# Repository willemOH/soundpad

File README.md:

Soundpad: tactile sampler instrument and sound sketchpad

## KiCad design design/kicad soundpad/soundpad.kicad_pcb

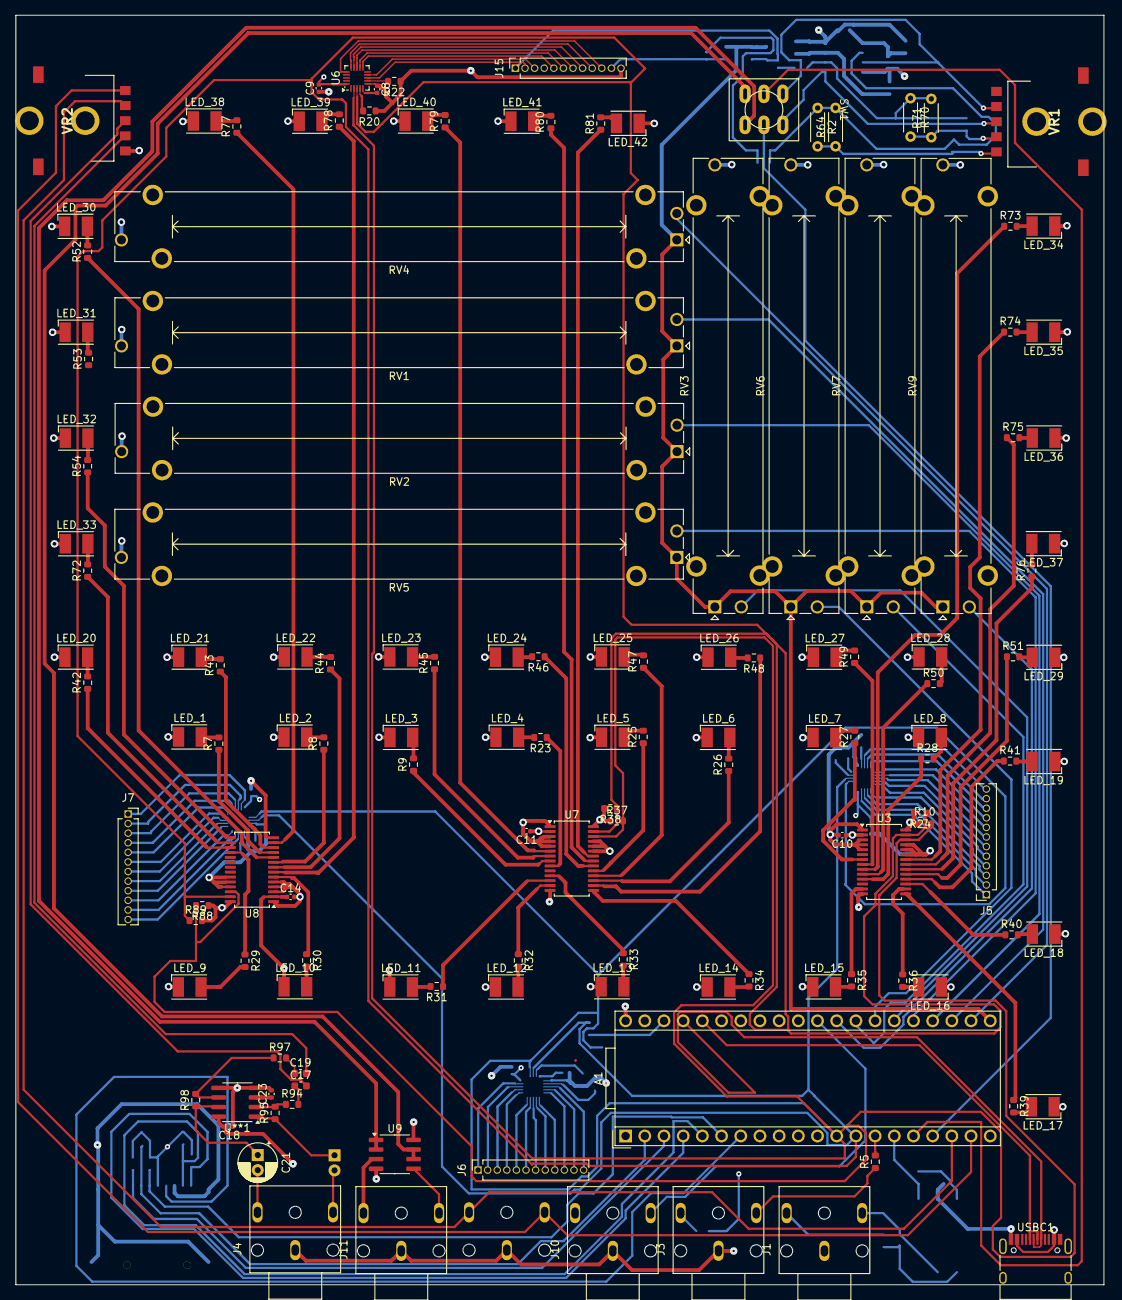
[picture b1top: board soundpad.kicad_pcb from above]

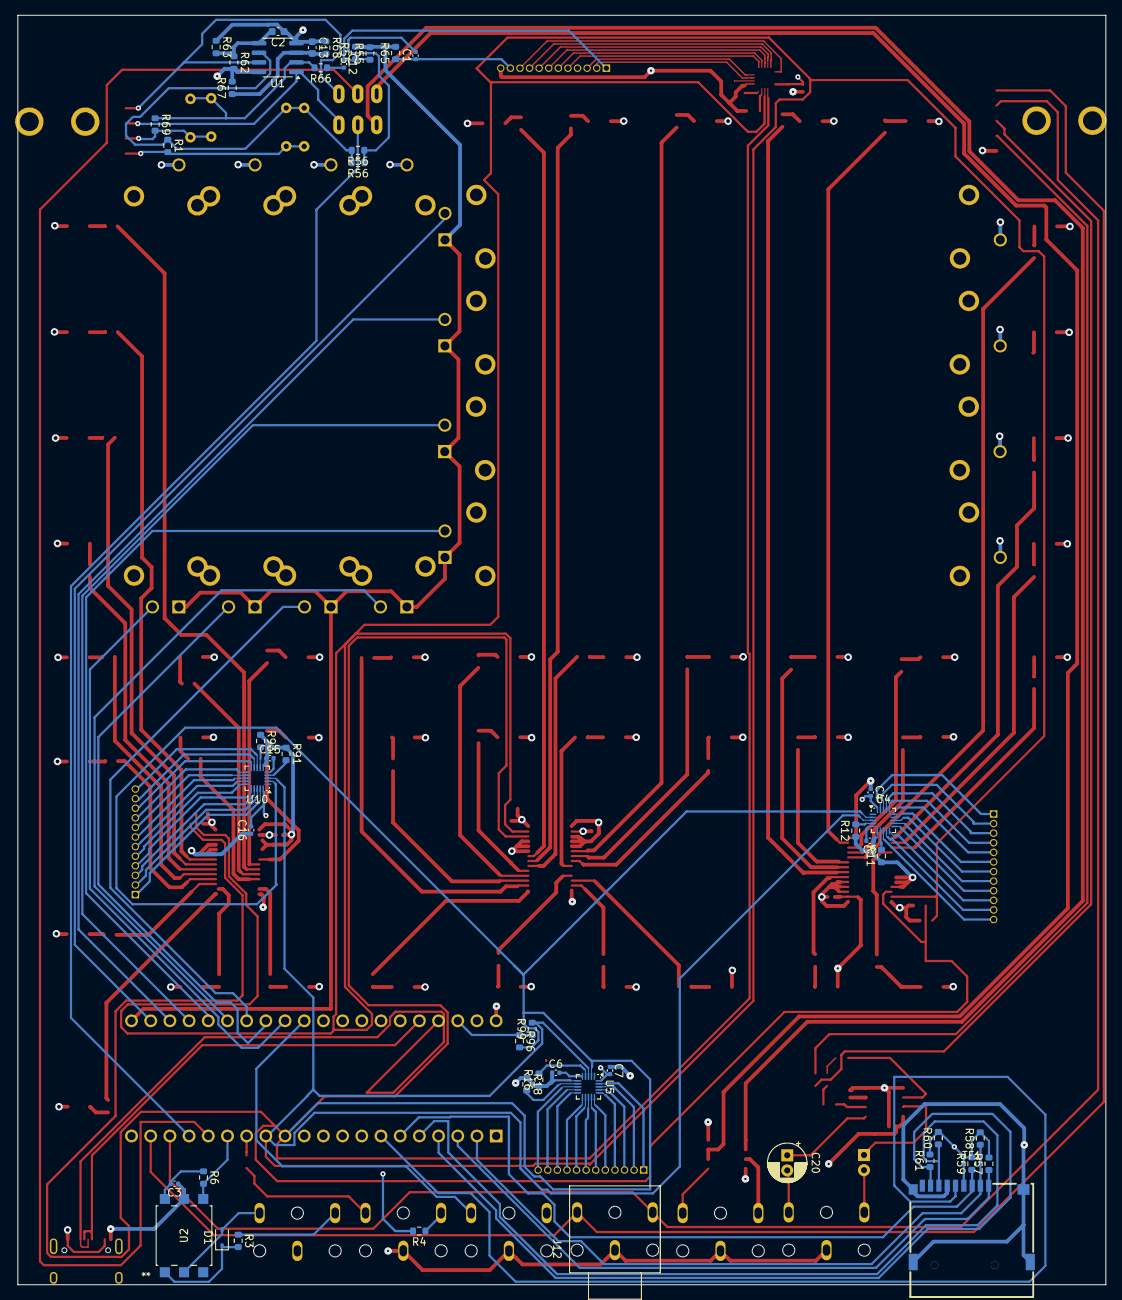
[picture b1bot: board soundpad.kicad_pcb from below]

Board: 4 copper layers, 144.0 x 168.0 mm, 187 parts (48 on the bottom side), 201 nets.

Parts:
A1: Electrosmith_Daisy_Seed_Rev4; Electrosmith_Daisy_Seed
C1, C3, C4, C5, C6, C7, C8, C9, C10, C11, C12, C14, C15, C16, C18, C23: 0.1uF; C_0402_1005Metric
C2, C13: 10uF; C_0603_1608Metric
C17, C19: .47uF; C_0603_1608Metric
C20, C21: 220UF PANASONIC D8; CP_Radial_D5.0mm_P2.00mm
D1: 1N4148WS; D_SOD-323
J1: Midi_In; CUI_SJ1-3553NG
J3: Midi_Out; CUI_SJ1-3553NG
J4: Headphone_Out; CUI_SJ1-3553NG
J5, J6, J7, J15: Conn_01x12_Socket; PinSocket_1x12_P1.27mm_Vertical
J10: Clock_Out; CUI_SJ1-3553NG
J11: Line_In; CUI_SJ1-3553NG
J12: Line_Out; CUI_SJ1-3553NG
LED_1, LED_2, LED_3, LED_4, LED_5, LED_6, LED_7, LED_8, LED_9, LED_10, LED_11, LED_12, LED_13, LED_14, LED_15, LED_16, LED_17, LED_18, LED_19, LED_20, LED_21, LED_22, LED_23, LED_24, LED_25, LED_26, LED_27, LED_28, LED_29, LED_30, LED_31, LED_32, LED_33, LED_34, LED_35, LED_36, LED_37, LED_38, LED_39, LED_40, LED_41, LED_42: White; LED_PLCC-2_3.4x3.0mm_AK
R1, R69: 10K; R_0603_1608Metric
R2, R64, R70, R71: DI*; R_Axial_DIN0204_L3.6mm_D1.6mm_P5.08mm_Horizontal
R3: 220R; R_0603_1608Metric
R4: 33R; R_0603_1608Metric
R5: 10R; R_0603_1608Metric
R6: 270R; R_0603_1608Metric
R7, R8, R9, R23, R25, R26, R27, R28, R29, R30, R31, R32, R33, R34, R35, R36, R39, R40, R41, R42, R43, R44, R45, R46, R47, R48, R49, R50, R51, R52, R53, R54, R72, R73, R74, R75, R76, R77, R78, R79, R80, R81: 140R; R_0603_1608Metric
R10, R24, R37, R38, R88, R89: 4.7K; R_0603_1608Metric
R11, R18, R22, R93: 75k; R_0603_1608Metric
R12, R16, R20, R91: 100k; R_0603_1608Metric
R55, R55#2, R65: 2.2K; R_0603_1608Metric
R56, R56#2, R66: 50R; R_0603_1608Metric
R57, R58, R59, R60, R61: 47k; R_0603_1608Metric
R62, R63, R67, R68: 100K; R_0603_1608Metric
R94, R97: 22K; R_0603_1608Metric
R95, R98: 33K; R_0603_1608Metric
R96, R99: 10k; R_0603_1608Metric
RV1: slider2; Potentiometer_Bourns_PTA6043_Single_Slide
RV2: slider3; Potentiometer_Bourns_PTA6043_Single_Slide
RV3: sliderA; Potentiometer_Bourns_PTA4543_Single_Slide
RV4: slider1; Potentiometer_Bourns_PTA6043_Single_Slide
RV5: slider4; Potentiometer_Bourns_PTA6043_Single_Slide
RV6: sliderB; Potentiometer_Bourns_PTA4543_Single_Slide
RV7: sliderC; Potentiometer_Bourns_PTA4543_Single_Slide
RV9: sliderD; Potentiometer_Bourns_PTA4543_Single_Slide
SW1: SW_DPDT_x2; Toggle Submini DPDT Prongs
TF1: TF-CARD H1.8; TF-SMD_TF-CARD-H1.8
U1, U9: MCP6002-xSN; SOIC-8_3.9x4.9mm_P1.27mm
U2: H11L1S(TA); H11L1STA_EVE
U3, U7, U8: PCA9685PW; TSSOP-28_4.4x9.7mm_P0.65mm
U4, U5, U6, U10: MPR121QR2; UQFN-20_3x3mm_P0.4mm
U**1: LM4881MX SOIC-8; SOIC-8_3.9x4.9mm_P1.27mm
USBC1: TYPE-C-31-M-12; USB_C_Receptacle_HRO_TYPE-C-31-M-12
VR1, VR2: RK10J12R0A0B

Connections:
3V3_A: A1.21 (3V3_A), C18.2, R55.2, R55#2.2, R65.2, RV1.1, RV2.1, RV3.1, RV4.1, RV5.1, RV6.1, RV7.1, RV9.1, U**1.8 (VCC)
3V3_D: A1.38 (3V3_D), C4.2, C7.2, C9.2, C16.2, R4.2, R57.2, R58.2, R59.2, R60.2, R61.2, R96.1, R99.1, TF1.4 (VDD), U4.20 (VDD), U5.20 (VDD), U6.20 (VDD), U10.20 (VDD)
5V: A1.39 (VIN), C10.1, C11.1, C14.1, LED_1.2 (A), LED_2.2 (A), LED_3.2 (A), LED_4.2 (A), LED_5.2 (A), LED_6.2 (A), LED_7.2 (A), LED_8.2 (A), LED_9.2 (A), LED_10.2 (A), LED_11.2 (A), LED_12.2 (A), LED_13.2 (A), LED_14.2 (A), LED_15.2 (A), LED_16.2 (A), LED_17.2 (A), LED_18.2 (A), LED_19.2 (A), LED_20.2 (A), LED_21.2 (A), LED_22.2 (A), LED_23.2 (A), LED_24.2 (A), LED_25.2 (A), LED_26.2 (A), LED_27.2 (A), LED_28.2 (A), LED_29.2 (A), LED_30.2 (A), LED_31.2 (A), LED_32.2 (A), LED_33.2 (A), LED_34.2 (A), LED_35.2 (A), LED_36.2 (A), LED_37.2 (A), LED_38.2 (A), LED_39.2 (A), LED_40.2 (A), LED_41.2 (A), LED_42.2 (A), R10.2, R24.2, R37.2, R38.2, R62.2, R67.2, R88.2, R89.2, U1.8 (V+), U3.2 (A1), U3.28 (VDD), U7.2 (A1), U7.28 (VDD), U8.2 (A1), U8.28 (VDD), U9.8 (V+), USBC1.A4 (VBUS), USBC1.A9 (VBUS), USBC1.B4 (VBUS), USBC1.B9 (VBUS)
+3.3V: C3.2, R6.1, U2.6
/Audio_IO/Headphone_Out_L: C20.2, J4.T
/Audio_IO/Headphone_Out_R: C21.2, J4.R
/Audio_IO/Headphone_Wiper_L: C17.2, VR2.2 (2_1)
/Audio_IO/Headphone_Wiper_R: C19.2, VR2.4 (2_2)
/IO_SDcard/Line_In_L: SW1.3 (C), U9.6 (-), U9.7
/IO_SDcard/Line_In_R: SW1.6 (C), U9.1, U9.2 (-)
/IO_SDcard/mic_out_L: SW1.1 (A), U1.7, VR1.4 (2_2)
/IO_SDcard/mic_out_R: SW1.4 (A), U1.1, VR1.2 (2_1)
/LEDs/LED_1: R7.1, U8.11 (LED5)
/LEDs/LED_2: R8.1, U8.9 (LED3)
/LEDs/LED_3: R9.1, U7.8 (LED2)
/LEDs/LED_4: R23.1, U7.9 (LED3)
/LEDs/LED_5: R25.1, U7.19 (LED12)
/LEDs/LED_6: R26.1, U7.17 (LED10)
/LEDs/LED_7: R27.1, U3.7 (LED1)
/LEDs/LED_8: R28.1, U3.11 (LED5)
/LEDs/LED_9: R29.1, U8.18 (LED11)
/LEDs/LED_10: R30.1, U8.6 (LED0)
/LEDs/LED_11: R31.1, U7.12 (LED6)
/LEDs/LED_12: R32.1, U7.13 (LED7)
/LEDs/LED_13: R33.1, U7.11 (LED5)
/LEDs/LED_14: R34.1, U7.15 (LED8)
/LEDs/LED_15: R35.1, U3.13 (LED7)
/LEDs/LED_16: R36.1, U3.16 (LED9)
/LEDs/LED_17: R39.1, U3.15 (LED8)
/LEDs/LED_18: R40.1, U3.17 (LED10)
/LEDs/LED_19: R41.1, U3.18 (LED11)
/LEDs/LED_20: R42.1, U8.17 (LED10)
/LEDs/LED_21: R43.1, U8.12 (LED6)
/LEDs/LED_22: R44.1, U8.8 (LED2)
/LEDs/LED_23: R45.1, U7.7 (LED1)
/LEDs/LED_24: R46.1, U7.20 (LED13)
/LEDs/LED_25: R47.1, U7.18 (LED11)
/LEDs/LED_26: R48.1, U7.16 (LED9)
/LEDs/LED_27: R49.1, U3.8 (LED2)
/LEDs/LED_28: R50.1, U3.10 (LED4)
/LEDs/LED_29: R51.1, U3.19 (LED12)
/LEDs/LED_30: R52.1, U8.10 (LED4)
/LEDs/LED_32: R54.1, U8.15 (LED8)
/LEDs/LED_33: R72.1, U8.16 (LED9)
/LEDs/LED_34: R73.1, U3.9 (LED3)
/LEDs/LED_35: R74.1, U3.22 (LED15)
/LEDs/LED_36: R75.1, U3.21 (LED14)
/LEDs/LED_37: R76.1, U3.20 (LED13)
/LEDs/LED_38: R77.1, U8.13 (LED7)
/LEDs/LED_39: R78.1, U8.7 (LED1)
/LEDs/LED_40: R79.1, U7.6 (LED0)
/LEDs/LED_41: R80.1, U7.21 (LED14)
/LEDs/LED_42: R81.1, U7.22 (LED15)
AMP: J7.5, U4.15 (LED3/ELE7)
Audio_in_1: A1.16 (AUDIO_IN_1), SW1.2 (B)
Audio_in_2: A1.17 (AUDIO_IN_2), SW1.5 (B)
Audio_out_1: A1.18 (AUDIO_OUT_1), J12.T, VR2.3 (3_1)
Audio_out_2: A1.19 (AUDIO_OUT_2), J12.R, VR2.5 (3_2)
COMP: J5.7, U10.13 (LED1/ELE5)
Clock_out: A1.30 (DAC_OUT1), J10.T
D+: A1.37 (USB_D_+), USBC1.A6 (DP1), USBC1.B6 (DP2)
D-: A1.36 (USB_D_-), USBC1.A7 (DN1), USBC1.B7 (DN2)
EFFCT: J5.6, U10.14 (LED2/ELE6)
Extra1: J6.8, U5.12 (LED0/ELE4)
Extra2: J6.9, U5.11 (ELE3)
Extra3: J6.10, U5.10 (ELE2)
FILT: J7.6, U4.14 (LED2/ELE6)
GND: A1.20 (AGND), A1.40 (DGND), C2.1, C3.1, C4.1, C5.1, C6.1, C7.1, C8.1, C9.1, C10.2, C11.2, C13.1, C14.2, C15.1, C16.1, C18.1, C23.2, J3.S, J4.S, J10.S, J11.S, J12.S, J15.12, R11.1, R12.1, R16.1, R18.1, R20.1, R22.1, R63.1, R68.1, R91.1, R93.1, RV1.3, RV2.3, RV3.3, RV4.3, RV5.3, RV6.3, RV7.3, RV9.3, TF1.6 (VSS), TF1.10 (GND), TF1.11 (GND), TF1.12 (GND), TF1.13 (GND), U1.4 (V-), U2.5, U3.1 (A0), U3.3 (A2), U3.4 (A3), U3.5 (A4), U3.14 (VSS), U3.23 (~OE), U3.24 (A5), U3.25 (EXTCLK), U4.6 (VSS), U5.6 (VSS), U6.6 (VSS), U7.1 (A0), U7.3 (A2), U7.4 (A3), U7.5 (A4), U7.14 (VSS), U7.23 (~OE), U7.24 (A5), U7.25 (EXTCLK), U8.1 (A0), U8.3 (A2), U8.4 (A3), U8.5 (A4), U8.14 (VSS), U8.23 (~OE), U8.24 (A5), U8.25 (EXTCLK), U9.4 (V-), U10.6 (VSS), U**1.4 (GND), U**1.5 (SDOWN), USBC1.A1 (GND), USBC1.B12 (GND), VR2.1 (1/1)
MIDI_RX: A1.15 (USART1_RX), R6.2, U2.4
MIDI_TX: A1.14 (USART1_TX), R5.2
MOD: J7.7, U4.13 (LED1/ELE5)
MicL: C1.1, J15.11, R65.1
MicR: C12.1, J15.1, R55.1, R55#2.1
unnamed: A1.22 (ADC_0), RV4.2
unnamed: A1.23 (ADC_1), RV1.2
unnamed: A1.24 (ADC_2), RV2.2
unnamed: A1.25 (ADC_3), RV5.2
unnamed: A1.26 (ADC_4), RV3.2
unnamed: A1.27 (ADC_5), RV6.2
unnamed: A1.28 (ADC_6), RV7.2
unnamed: A1.29 (DAC_OUT2), RV9.2
unnamed: C1.2, R56.1, R56#2.1
unnamed: C12.2, R66.1
unnamed: C17.1, R94.2
unnamed: C19.1, R97.2
unnamed: D1.2 (A), J1.T, U2.2
unnamed: D1.1 (K), R3.2, U2.1
unnamed: J1.R, R3.1
unnamed: J3.R, R4.1
unnamed: J3.T, R5.1
unnamed: LED_1.1 (K), R7.2
unnamed: LED_2.1 (K), R8.2
unnamed: LED_3.1 (K), R9.2
unnamed: LED_4.1 (K), R23.2
unnamed: LED_5.1 (K), R25.2
unnamed: LED_6.1 (K), R26.2
unnamed: LED_7.1 (K), R27.2
unnamed: LED_8.1 (K), R28.2
unnamed: LED_9.1 (K), R29.2
unnamed: LED_10.1 (K), R30.2
unnamed: LED_11.1 (K), R31.2
unnamed: LED_12.1 (K), R32.2
unnamed: LED_13.1 (K), R33.2
unnamed: LED_14.1 (K), R34.2
unnamed: LED_15.1 (K), R35.2
unnamed: LED_16.1 (K), R36.2
unnamed: LED_17.1 (K), R39.2
unnamed: LED_18.1 (K), R40.2
unnamed: LED_19.1 (K), R41.2
unnamed: LED_20.1 (K), R42.2
unnamed: LED_21.1 (K), R43.2
unnamed: LED_22.1 (K), R44.2
unnamed: LED_23.1 (K), R45.2
unnamed: LED_24.1 (K), R46.2
unnamed: LED_25.1 (K), R47.2
unnamed: LED_26.1 (K), R48.2
unnamed: LED_27.1 (K), R49.2
unnamed: LED_28.1 (K), R50.2
unnamed: LED_29.1 (K), R51.2
unnamed: LED_30.1 (K), R52.2
unnamed: LED_31.1 (K), R53.2
unnamed: LED_32.1 (K), R54.2
unnamed: LED_33.1 (K), R72.2
unnamed: LED_34.1 (K), R73.2
unnamed: LED_35.1 (K), R74.2
unnamed: LED_36.1 (K), R75.2
unnamed: LED_37.1 (K), R76.2
unnamed: LED_38.1 (K), R77.2
unnamed: LED_39.1 (K), R78.2
unnamed: LED_40.1 (K), R79.2
unnamed: LED_41.1 (K), R80.2
unnamed: LED_42.1 (K), R81.2
unnamed: C13.2, R67.1, R68.2, U1.3 (+)
unnamed: R66.2, R69.1, R70.1, R71.2, U1.2 (-)
unnamed: C2.2, R62.1, R63.2, U1.5 (+)
unnamed: R1.1, R2.1, R56.2, R56#2.2, R64.2, U1.6 (-)
unnamed: R12.2, U4.4 (ADDR)
unnamed: R11.2, U4.7 (REXT)
unnamed: C5.2, U4.5 (VREG)
unnamed: R16.2, U5.4 (ADDR)
unnamed: R18.2, U5.7 (REXT)
unnamed: C6.2, U5.5 (VREG)
unnamed: R20.2, U6.4 (ADDR)
unnamed: R22.2, U6.7 (REXT)
unnamed: C8.2, U6.5 (VREG)
unnamed: J11.R, U9.3 (+)
unnamed: J11.T, U9.5 (+)
unnamed: R91.2, U10.4 (ADDR)
unnamed: R93.2, U10.7 (REXT)
unnamed: C15.2, U10.5 (VREG)
unnamed: C23.1, U**1.3 (BPASS)
unnamed: R94.1, R95.2, U**1.2 (IN1)
unnamed: R97.1, R98.2, U**1.6 (IN2)
unnamed: C20.1, R95.1, U**1.1 (OUT1)
unnamed: C21.1, R98.1, U**1.7 (OUT2)
unnamed: R69.2, R70.2, R71.1, VR1.3 (3_1)
unnamed: R1.2, R2.2, R64.1, VR1.5 (3_2)
POUCH: J5.9, U10.11 (ELE3)
Pad1: J7.11, U4.9 (ELE1)
Pad2: J7.10, U4.10 (ELE2)
Pad3: J7.9, U4.11 (ELE3)
Pad4: J7.8, U4.12 (LED0/ELE4)
Pad5: J5.5, U10.15 (LED3/ELE7)
Pad6: J5.4, U10.16 (LED4/ELE8)
Pad7: J5.3, U10.17 (LED5/ELE9)
Pad8: J5.2, U10.18 (LED6/ELE10)
Pad9: J7.12, U4.8 (ELE0)
Pad10: J6.1, U5.19 (LED7/ELE11)
Pad11: J6.2, U5.18 (LED6/ELE10)
Pad12: J6.3, U5.17 (LED5/ELE9)
Pad13: J6.4, U5.16 (LED4/ELE8)
Pad14: J6.5, U5.15 (LED3/ELE7)
Pad15: J6.6, U5.14 (LED2/ELE6)
Pad16: J6.7, U5.13 (LED1/ELE5)
PadAfter: J15.8, U6.14 (LED2/ELE6)
PadEmpty: J5.10, U10.10 (ELE2)
PadFlow: J15.5, U6.11 (ELE3)
PadGroups: J5.1, U10.19 (LED7/ELE11)
PadL1: J15.10, U6.16 (LED4/ELE8)
PadL2: J15.9, U6.15 (LED3/ELE7)
PadL3: J7.1, U4.19 (LED7/ELE11)
PadL4: J7.2, U4.18 (LED6/ELE10)
PadMod: J15.6, U6.12 (LED0/ELE4)
PadNotes: J6.12, U5.8 (ELE0)
PadPattern: J6.11, U5.9 (ELE1)
PadPocket: J7.3, U4.17 (LED5/ELE9)
PadR1: J15.2, U6.8 (ELE0)
PadR2: J15.3, U6.9 (ELE1)
PadR3: J5.12, U10.8 (ELE0)
PadR4: J5.11, U10.9 (ELE1)
PadVelo: J15.7, U6.13 (LED1/ELE5)
SCL: A1.12 (I2C1_SCL), R10.1, R37.1, R88.1, R96.2, U3.26 (SCL), U4.2 (SCL), U5.2 (SCL), U6.2 (SCL), U7.26 (SCL), U8.26 (SCL), U10.2 (SCL)
SCRATCH: J5.8, U10.12 (LED0/ELE4)
SDA: A1.13 (I2C1_SDA), R24.1, R38.1, R89.1, R99.2, U3.27 (SDA), U4.3 (SDA), U5.3 (SDA), U6.3 (SDA), U7.27 (SDA), U8.27 (SDA), U10.3 (SDA)
SD_CK: A1.7 (SD_CLK), TF1.5 (CLK)
SD_CMD: A1.6 (SD_CMD), R59.1, TF1.3 (CMD)
SD_D0: A1.5 (SD_DATA_0), R60.1, TF1.7 (DAT0)
SD_D1: A1.4 (SD_DATA_1), R61.1, TF1.8 (DAT1)
SD_D2: A1.3 (SD_DATA_2), R57.1, TF1.1 (DAT2)
SD_D3: A1.2 (SD_DATA_3), R58.1, TF1.2 (CD/DAT3)
SOUND: J7.4, U4.16 (LED4/ELE8)

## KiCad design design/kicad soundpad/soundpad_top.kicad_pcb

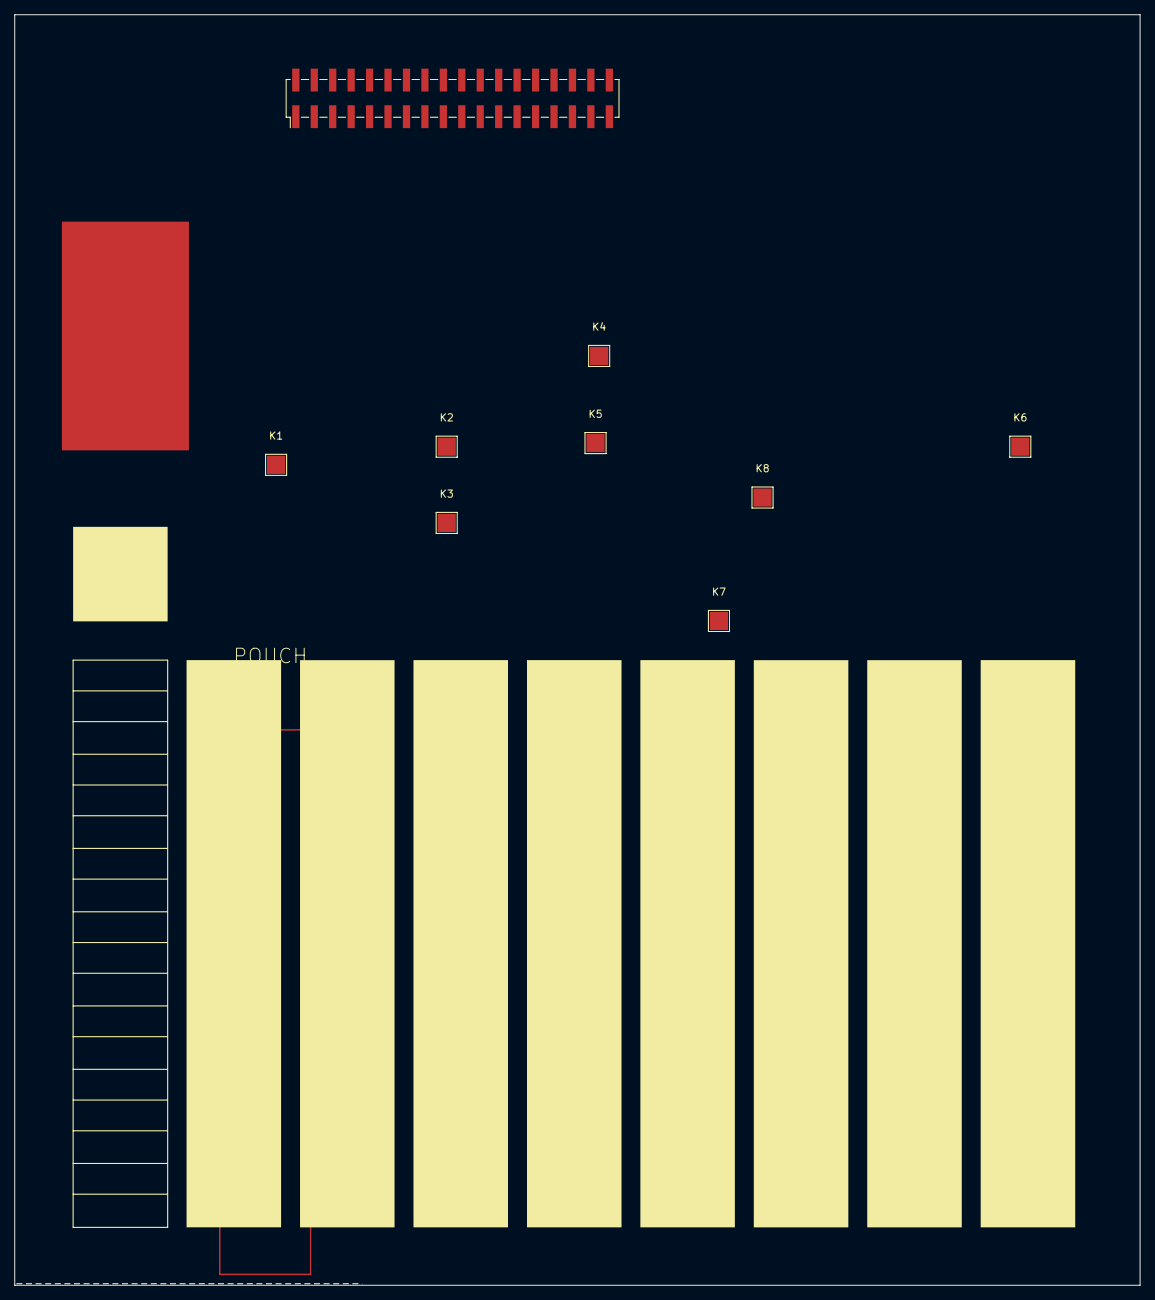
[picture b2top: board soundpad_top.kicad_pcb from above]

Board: 2 copper layers, 155.0 x 175.0 mm, 9 parts (0 on the bottom side), 8 nets, no tracks yet.

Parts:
J2: Conn_02x18_Counter_Clockwise; PinHeader_2x18_P2.54mm_Vertical_SMD
K1, K2, K3, K4, K5, K6, K7, K8: Conn_01x01; TestPoint_Pad_2.5x2.5mm

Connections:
unnamed: J2.1, K1.1
unnamed: J2.3, K2.1
unnamed: J2.5, K3.1
unnamed: J2.7, K4.1
unnamed: J2.9, K5.1
unnamed: J2.11, K6.1
unnamed: J2.13, K7.1
unnamed: J2.15, K8.1

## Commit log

2024-08-17 first
2024-08-17 tests button
2024-08-17 stops tracking build directory
2024-08-17 saving changes before continuing rebase
2024-08-17 updates readme to project mission
2024-08-17 adds .gitignore, untracks build dir, updates readme
2024-08-17 changes project name
2024-08-18 adds sampling base, audio pass through while button pressed
2024-08-18 adds serial monitoring
2024-08-18 solves buffer recording, playback, looping is now a one button app fun remixer that adds input to looping buffer whenever button is held down
2024-08-19 serial monitoring off by default
2024-08-24 'normal' looping sampler
2024-08-24 adds to .gitignore
2024-08-24 fixes test tone playback on start
2024-08-24 refactors for basic stereo buffer class
2024-08-24 refactors bufferStereo.h for encapsulation
2024-08-24 cleans up main.cpp
2024-08-24 Introduces buffer chunks
    Allocates sample index ranges (chunks) from main buffers to be accessed from one of 16 objects which handles that chunk. Current setup performs the same as previous; no limits to keep recording withi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
2024-08-25 renames chunk-related info
2024-09-24 refactors sampling engine to new class
2024-09-25 cleans up comments, indentations, brackets
2024-09-25 refactors for hardware and ui encapsulation
    known bugs as of commit # 882fd294f44948a071e54f15eadf9aa652485573 (refactors sampling engine to new class):
    - loop start point is incorrect on first playback
    - sometimes does not playback loop, seemingly moreso if loop recorded is shorter than previous one
2024-09-25 Fixes bug, improves logic, cleans comments
    fixes shorter recording blank bug, evens bufferchunks divisions, removes bugtesting comments and old logic commented out
2024-09-26 Removes observer pattern, stops logging
2024-09-26 Separates finally sample engine from main
2024-09-27 Adds signal reference passing, global hardware object, optional float printing
2024-09-27 adds dev log file
2024-09-27 Encapsulates sample engine more, turns off logging, tidies comments
2024-09-27 v0.1: live remixer
    button1: record, button2: playback, button2+button1: playback loop on, live audio comes through when playback is not engaged
2024-09-28 Added interface.drawio
2024-09-28 Adds design directory, moves interface file
2024-09-30 Adds plate connections to pcb board
2024-09-30 v0.1: live remixer standalone
    turns off debugging so program can run without monitor connection
2024-10-04 Adds slider controls for sample start and end
2024-10-04 Updates kicad schematic for prototyping
    not a full schematic just all necessary parts to check off for a mouser order to set up a capactive touch prototype with midi in, out, and mic in
2024-10-04 renames variables, adds future hardware, makes functions private
2024-10-05 reduces function call rate
2024-10-07 adds start and end preview
    when sliders are moved a certain amount, a short preview of where the slider is in the continuum of the sample is played. This preview depends slightly on whether it is the start or end slider moved.
2024-10-07 resets start and end on record. Optimizes variable setting
2024-10-07 Increases slider resolution when loop is on
    bypasses threshold value for slider to change start and end
2024-10-08 adds speed change
    speed changes and triggers playback with play button + slider 1
2024-10-08 adds note play and note transpose
    play button + slider 2 increases pitch of sample by a scaled note increment. Current bug: speed changes are not what is played but the speed + note increment. so what you hear is not what you get
2024-10-10 Refactors sample settings to own file, design comments
2024-10-11 Refactors playback in sample class to own class
    Messy but functional refactor setting the stage for multiple simultaneous playback processes (polyphony). Sample class functions change playback class members when setting start or end (not ideal)
2024-10-18 Refactors buttons for capacitive touch
    A proud bit of work I must say. Ui class is streamlined by using button numbers directly instead of a struct. Binary operations and raw arrays replace library and vector functions for greater computa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
2024-10-19 Fixes button mash bug, adds 12-button objects
    When mashing buttons (intentionally try to break it), a button would not be removed and get stuck in the array. This fix checks for that and resets the array. Also adding back in an enum class that g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
2024-10-19 adds sliders 3 and 4
2024-10-22 adds continuous speed change, 10 buttons controls, less combos, design notes
    commands distributed over more buttons with commands behavior refined to give expected auditory results. See sp_ui.cpp for new command assignments.
2024-10-22 adds record to sd card test
    will record to sd card whatever is going out audio callback and then save the file on button 10 press. Works pretty flawlessly when logging is enabled. When not, no sound comes through input unless a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
2024-10-23 changes sd writing duration to record duration
    whatever is recorded to buffer which 'record' button is pressed is now also written (or overwritten) to a new file on the sd card. Additonal WriteProcess() function added because Process() is called 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
2024-10-25 refactors buffer to be interleaved
    For the purposes of easier transfer to wav files and back. Additionally, sample time increased due to writing 16-bit (current wav management limitation) instead of 24-bit audio and new calculations (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
2024-11-06 design updates
2024-11-06 fixes no startup if no sd card
2024-11-08 Refactors design for flat schematic, adds capactive touch, LCSC parts
    did not use bss138 level shifters and regulated 3.3v supply from adafruit schematic because daisy seed already has 3.3v regulated supply and 5V is not used internally on seed
2024-11-08 Completes all capacitive touch schematic work
    3x capacitive touch ics and routing to pins
2024-11-12 adds LEDs to design schematic
2024-12-11 completes kicad schematic, starts pcb layout
2025-01-18 routes PCB all except PWR
2025-01-18 gitignore kicad backups
2025-01-18 PCB all routed, Moves top components to top file
2025-01-18 gitignore kicad top backups
2025-01-24 shortens SD data lines
2025-01-27 adds debug log categorization
    new function to encapsulate hardware logging, now a globally accessible function. More logging/conversion to new logging of buttons pressed
2025-01-29 pcb rules fixes, reroute suggestions
2025-01-31 PCB moves analog signals to back plane
    so that ground plane inbetween them and digital signals. Also moves digital signals away from back plane and instead weaves them between the two top planes.
2025-03-26 last commit before refactor repo: kicad mostly
